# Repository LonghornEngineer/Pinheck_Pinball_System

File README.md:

Pinheck_Pinball_System
======================

Pinball system based off the PIC32 and Parallax Propeller microcontrollers

Created by:  
Benjamin J. Heckendorn  
Charlie Emery   
Parker Dillmann  

The Longhorn Engineer

http://longhornengineer.com/

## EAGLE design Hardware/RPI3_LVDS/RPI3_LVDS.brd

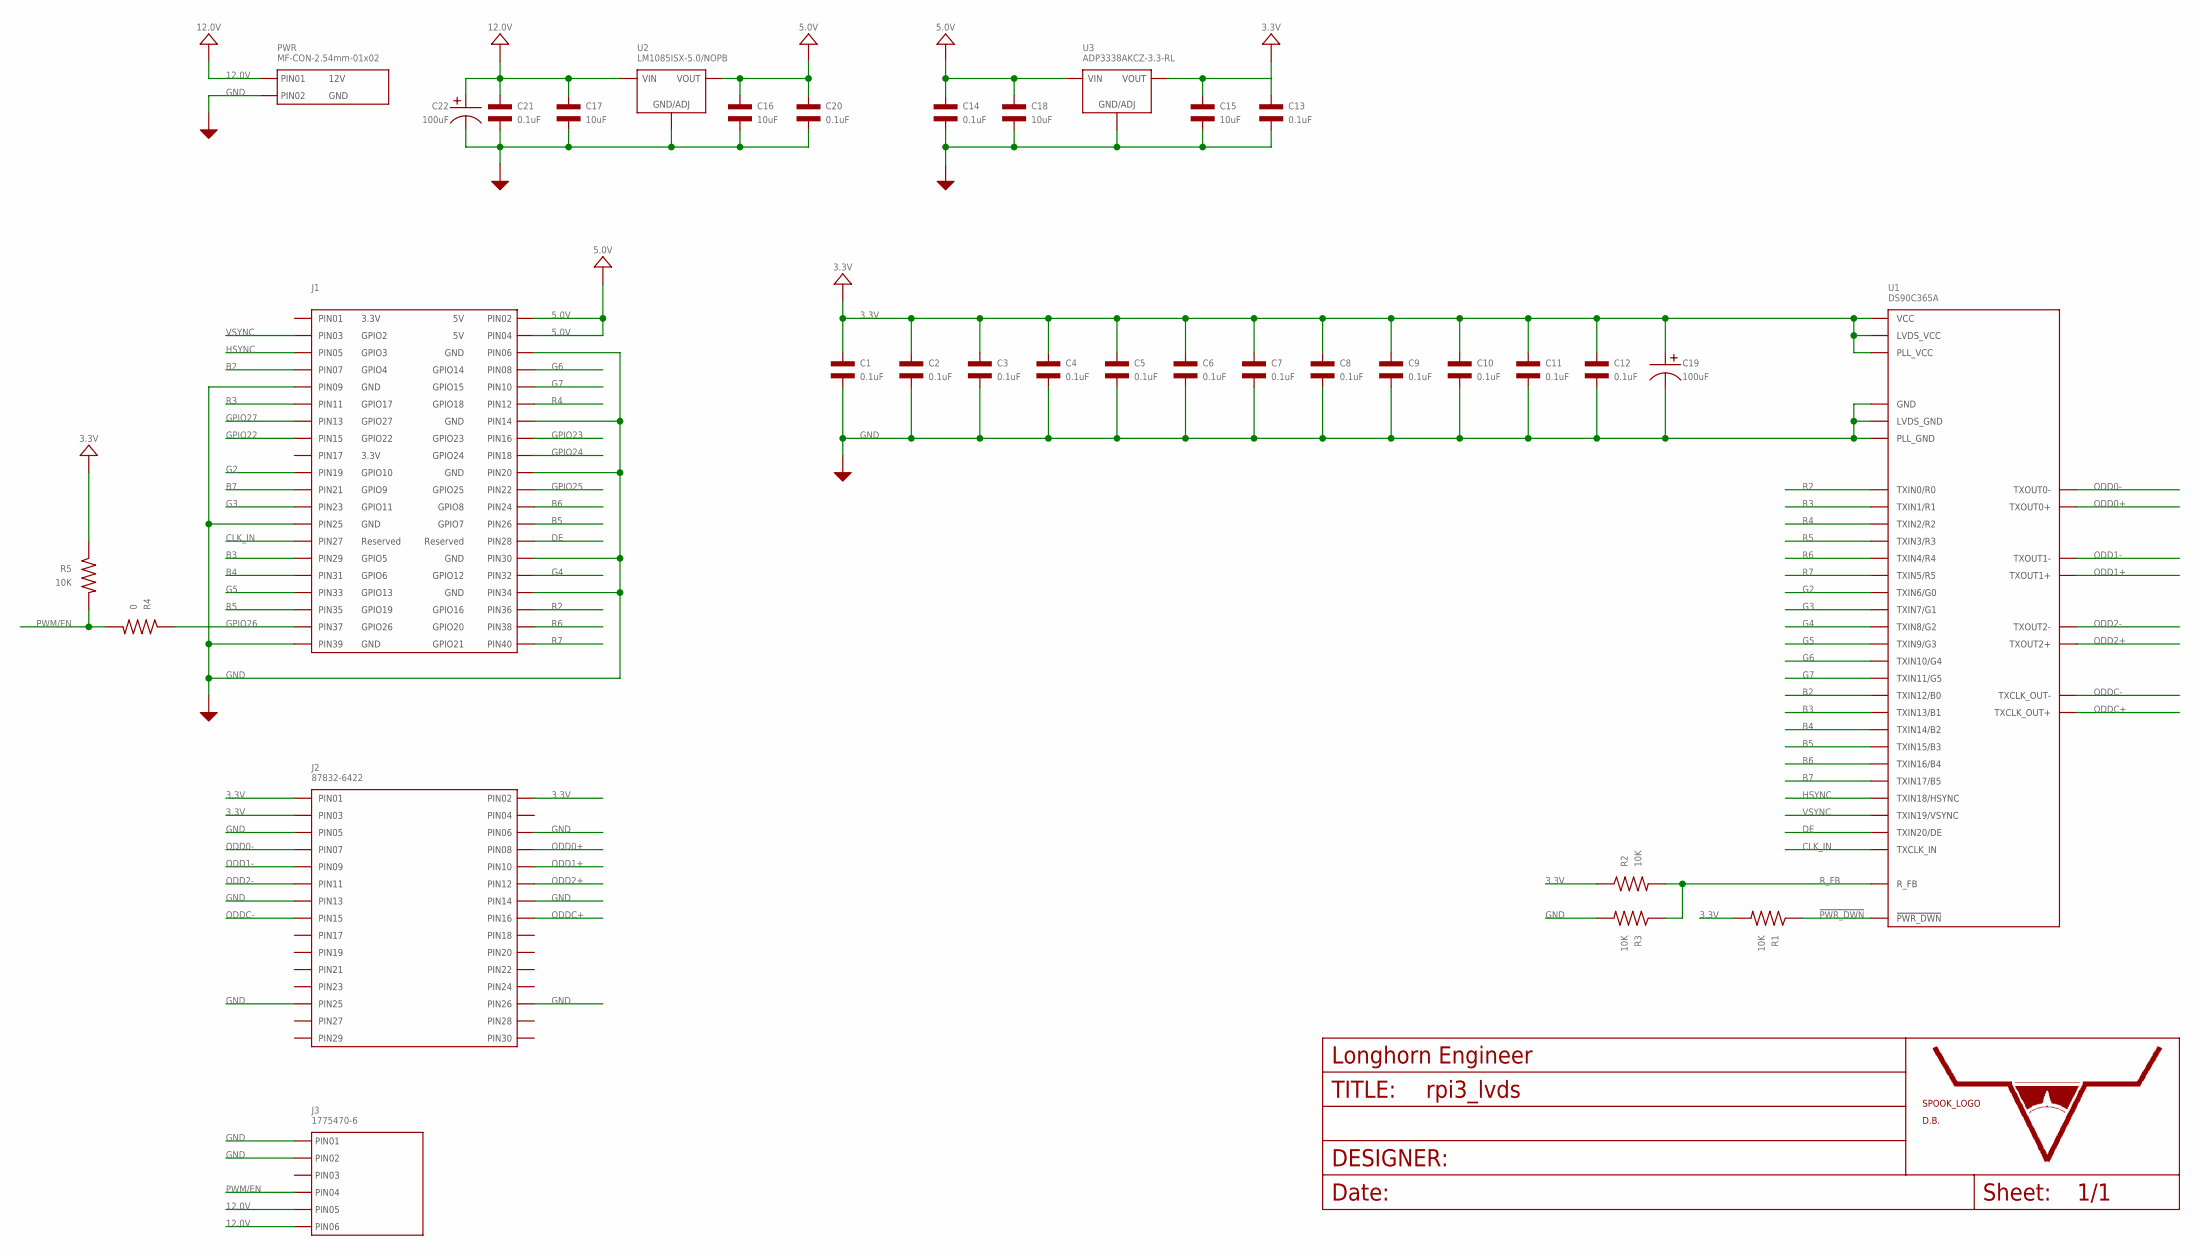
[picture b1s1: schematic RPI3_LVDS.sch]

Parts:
C1, C2, C3, C4, C5, C6, C7, C8, C9, C10, C11, C12, C13, C14, C20, C21: 0.1uF; C0603
C15, C16, C17, C18: 10uF; C1206
C19, C22: 100uF; CP6.3MM
J1: CON_02X202.54MM_PIN_HEADER; 2.54MM_02X20_PIN_HEADER
J2: 87832-6422
J3: 1775470-6
LOGO1: SPOOKY_LOGOSPOOKY_LOGO; SPOOKY_LOGO
PWR: MF-CON-2.54mm-01x02; PTH_2.54MM_01X02
R1, R2, R3, R5: 10K; R0603
R4: 0; R0603
U1: DS90C365A; DS90C365A_TSSOP-48
U2: LM1085ISX-5.0/NOPB; LM1085_TO-263-3
U3: ADP3338AKCZ-3.3-RL; ADP3338_SOT-223-3
U$14: LHE_FRAME
U$15: DB_LOGO_SILK_MEDIUM; DB_SILK_MEDIUM

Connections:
3.3V: C1.P$1, C2.P$1, C3.P$1, C4.P$1, C5.P$1, C6.P$1, C7.P$1, C8.P$1, C9.P$1, C10.P$1, C11.P$1, C12.P$1, C13.P$1, C15.P$1, C19.P$1, J2.P$1 (PIN0), J2.P$2 (PIN1), J2.P$3 (PIN2), R1.P$2, R2.P$1, R5.P$1, U1.P$2 (VCC), U1.P$8 (VCC), U1.P$21 (VCC), U1.P$29 (PLL_VCC), U1.P$37 (LVDS_VCC), U3.2 (OUT), U3.PAD (OUT)
5.0V: C14.P$1, C16.P$1, C18.P$1, C20.P$1, J1.2, J1.4, U2.P$2 (OUT), U2.P$4 (OUT), U3.3 (IN)
12.0V: C17.P$1, C21.P$1, C22.P$1, J3.P$5 (5), J3.P$6 (6), PWR.P$1 (PIN1), U2.P$3 (IN)
!PWR_DWN: R1.P$1, U1.P$27 (!PWR_DWN)
B2: J1.7, U1.P$13 (TXIN12/B0)
B3: J1.29, U1.P$15 (TXIN13/B1)
B4: J1.31, U1.P$16 (TXIN14/B2)
B5: J1.26, U1.P$18 (TXIN15/B3)
B6: J1.24, U1.P$19 (TXIN16/B4)
B7: J1.21, U1.P$20 (TXIN17/B5)
CLK_IN: J1.27, U1.P$26 (TXCLK_IN)
DE: J1.28, U1.P$25 (TXIN20/DE)
G2: J1.19, U1.P$4 (TXIN6/G0)
G3: J1.23, U1.P$6 (TXIN7/G1)
G4: J1.32, U1.P$7 (TXIN8/G2)
G5: J1.33, U1.P$9 (TXIN9/G3)
G6: J1.8, U1.P$10 (TXIN10/G4)
G7: J1.10, U1.P$12 (TXIN11/G5)
GND: C1.P$2, C2.P$2, C3.P$2, C4.P$2, C5.P$2, C6.P$2, C7.P$2, C8.P$2, C9.P$2, C10.P$2, C11.P$2, C12.P$2, C13.P$2, C14.P$2, C15.P$2, C16.P$2, C17.P$2, C18.P$2, C19.P$2, C20.P$2, C21.P$2, C22.P$2, J1.6, J1.9, J1.14, J1.20, J1.25, J1.30, J1.34, J1.39, J2.P$5 (PIN4), J2.P$6 (PIN5), J2.P$13 (PIN12), J2.P$14 (PIN13), J2.P$25 (PIN24), J2.P$26 (PIN25), J3.P$1 (1), J3.P$2 (2), PWR.P$2 (PIN2), R3.P$2, U1.P$5 (GND), U1.P$11 (GND), U1.P$17 (GND), U1.P$24 (GND), U1.P$28 (PLL_GND), U1.P$30 (PLL_GND), U1.P$31 (LVDS_GND), U1.P$36 (LVDS_GND), U1.P$42 (LVDS_GND), U1.P$46 (GND), U2.P$1 (GND), U3.1 (GND)
GPIO22: J1.15
GPIO23: J1.16
GPIO24: J1.18
GPIO25: J1.22
GPIO26: J1.37, R4.P$1
GPIO27: J1.13
HSYNC: J1.5, U1.P$22 (TXIN18/HSYNC)
ODD0+: J2.P$8 (PIN7), U1.P$40 (TXOUT0+)
ODD0-: J2.P$7 (PIN6), U1.P$41 (TXOUT0-)
ODD1+: J2.P$10 (PIN9), U1.P$38 (TXOUT1+)
ODD1-: J2.P$9 (PIN8), U1.P$39 (TXOUT1-)
ODD2+: J2.P$12 (PIN11), U1.P$34 (TXOUT2+)
ODD2-: J2.P$11 (PIN10), U1.P$35 (TXOUT2-)
ODDC+: J2.P$16 (PIN15), U1.P$32 (TXCLK_OUT+)
ODDC-: J2.P$15 (PIN14), U1.P$33 (TXCLK_OUT-)
PWM/EN: J3.P$4 (4), R4.P$2, R5.P$2
R2: J1.36, U1.P$44 (TXIN0/R0)
R3: J1.11, U1.P$45 (TXIN1/R1)
R4: J1.12, U1.P$47 (TXIN2/R2)
R5: J1.35, U1.P$48 (TXIN3/R3)
R6: J1.38, U1.P$1 (TXIN4/R4)
R7: J1.40, U1.P$3 (TXIN5/R5)
R_FB: R2.P$2, R3.P$1, U1.P$14 (R_FB)
VSYNC: J1.3, U1.P$23 (TXIN19/VSYNC)

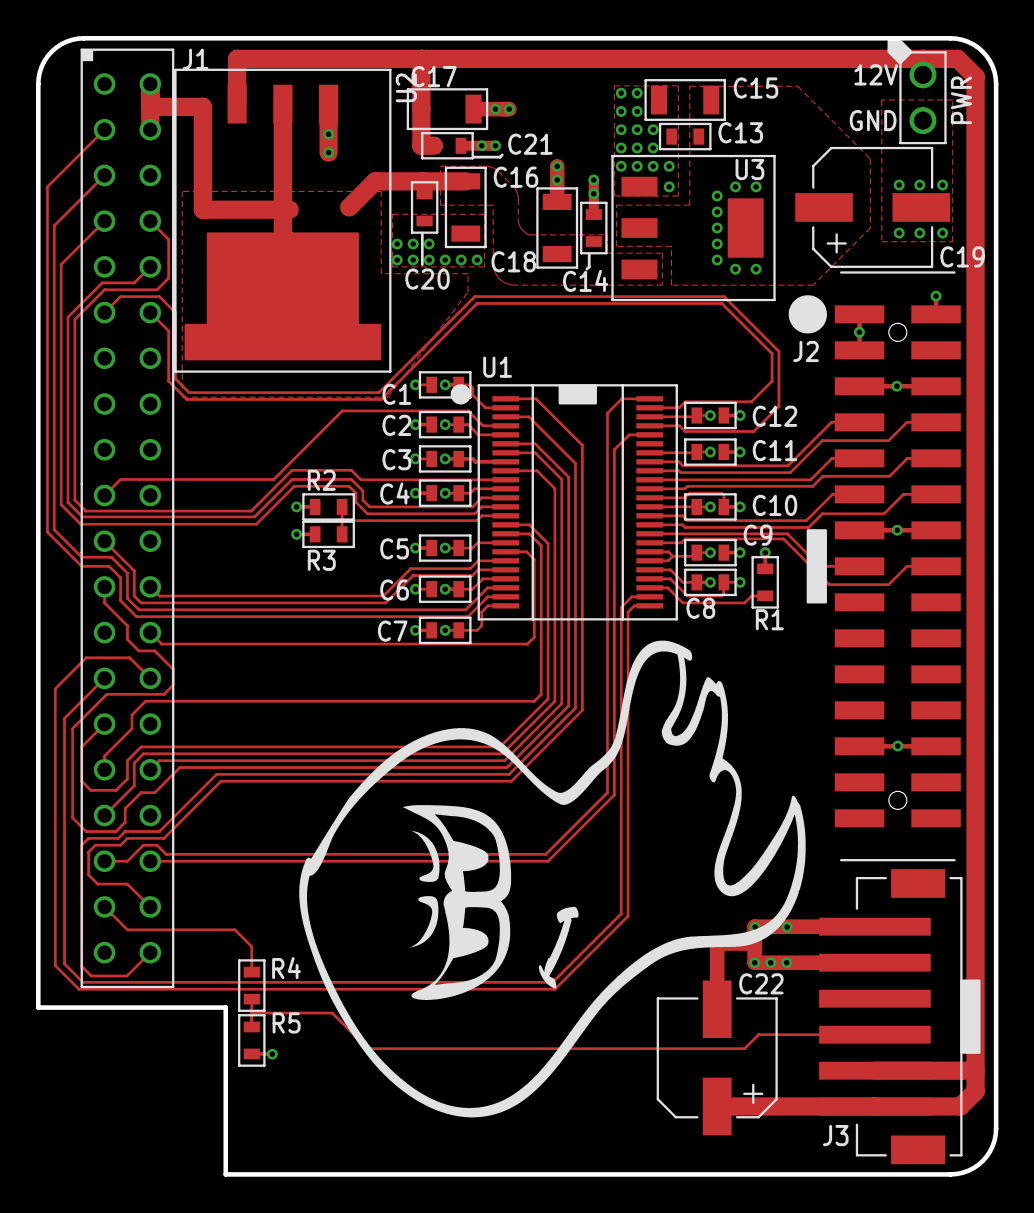
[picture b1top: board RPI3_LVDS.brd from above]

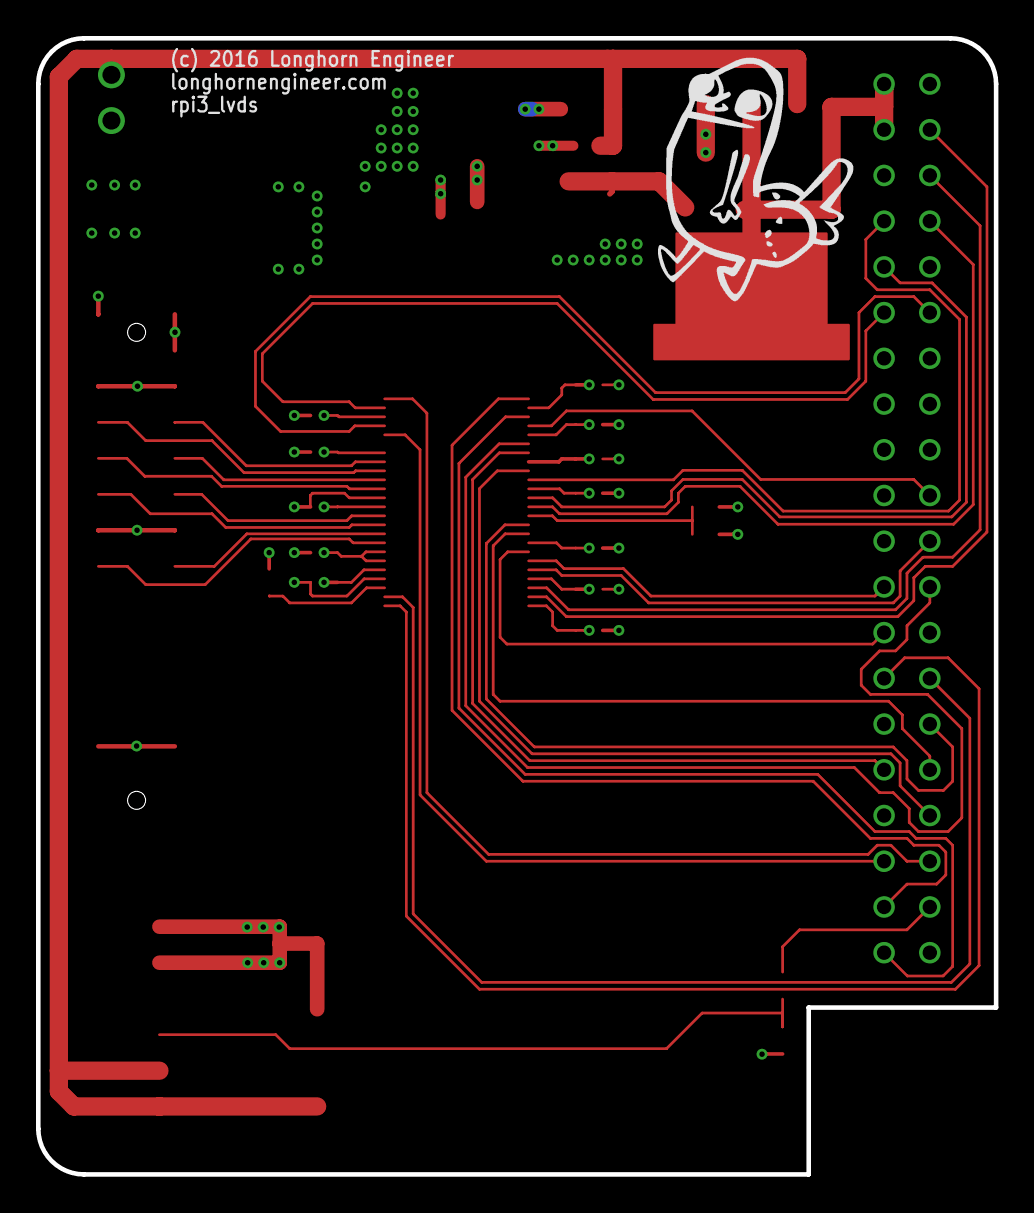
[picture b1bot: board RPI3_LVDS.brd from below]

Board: 4 copper layers, 53.2 x 63.1 mm, 37 parts (2 on the bottom side), 38 nets.

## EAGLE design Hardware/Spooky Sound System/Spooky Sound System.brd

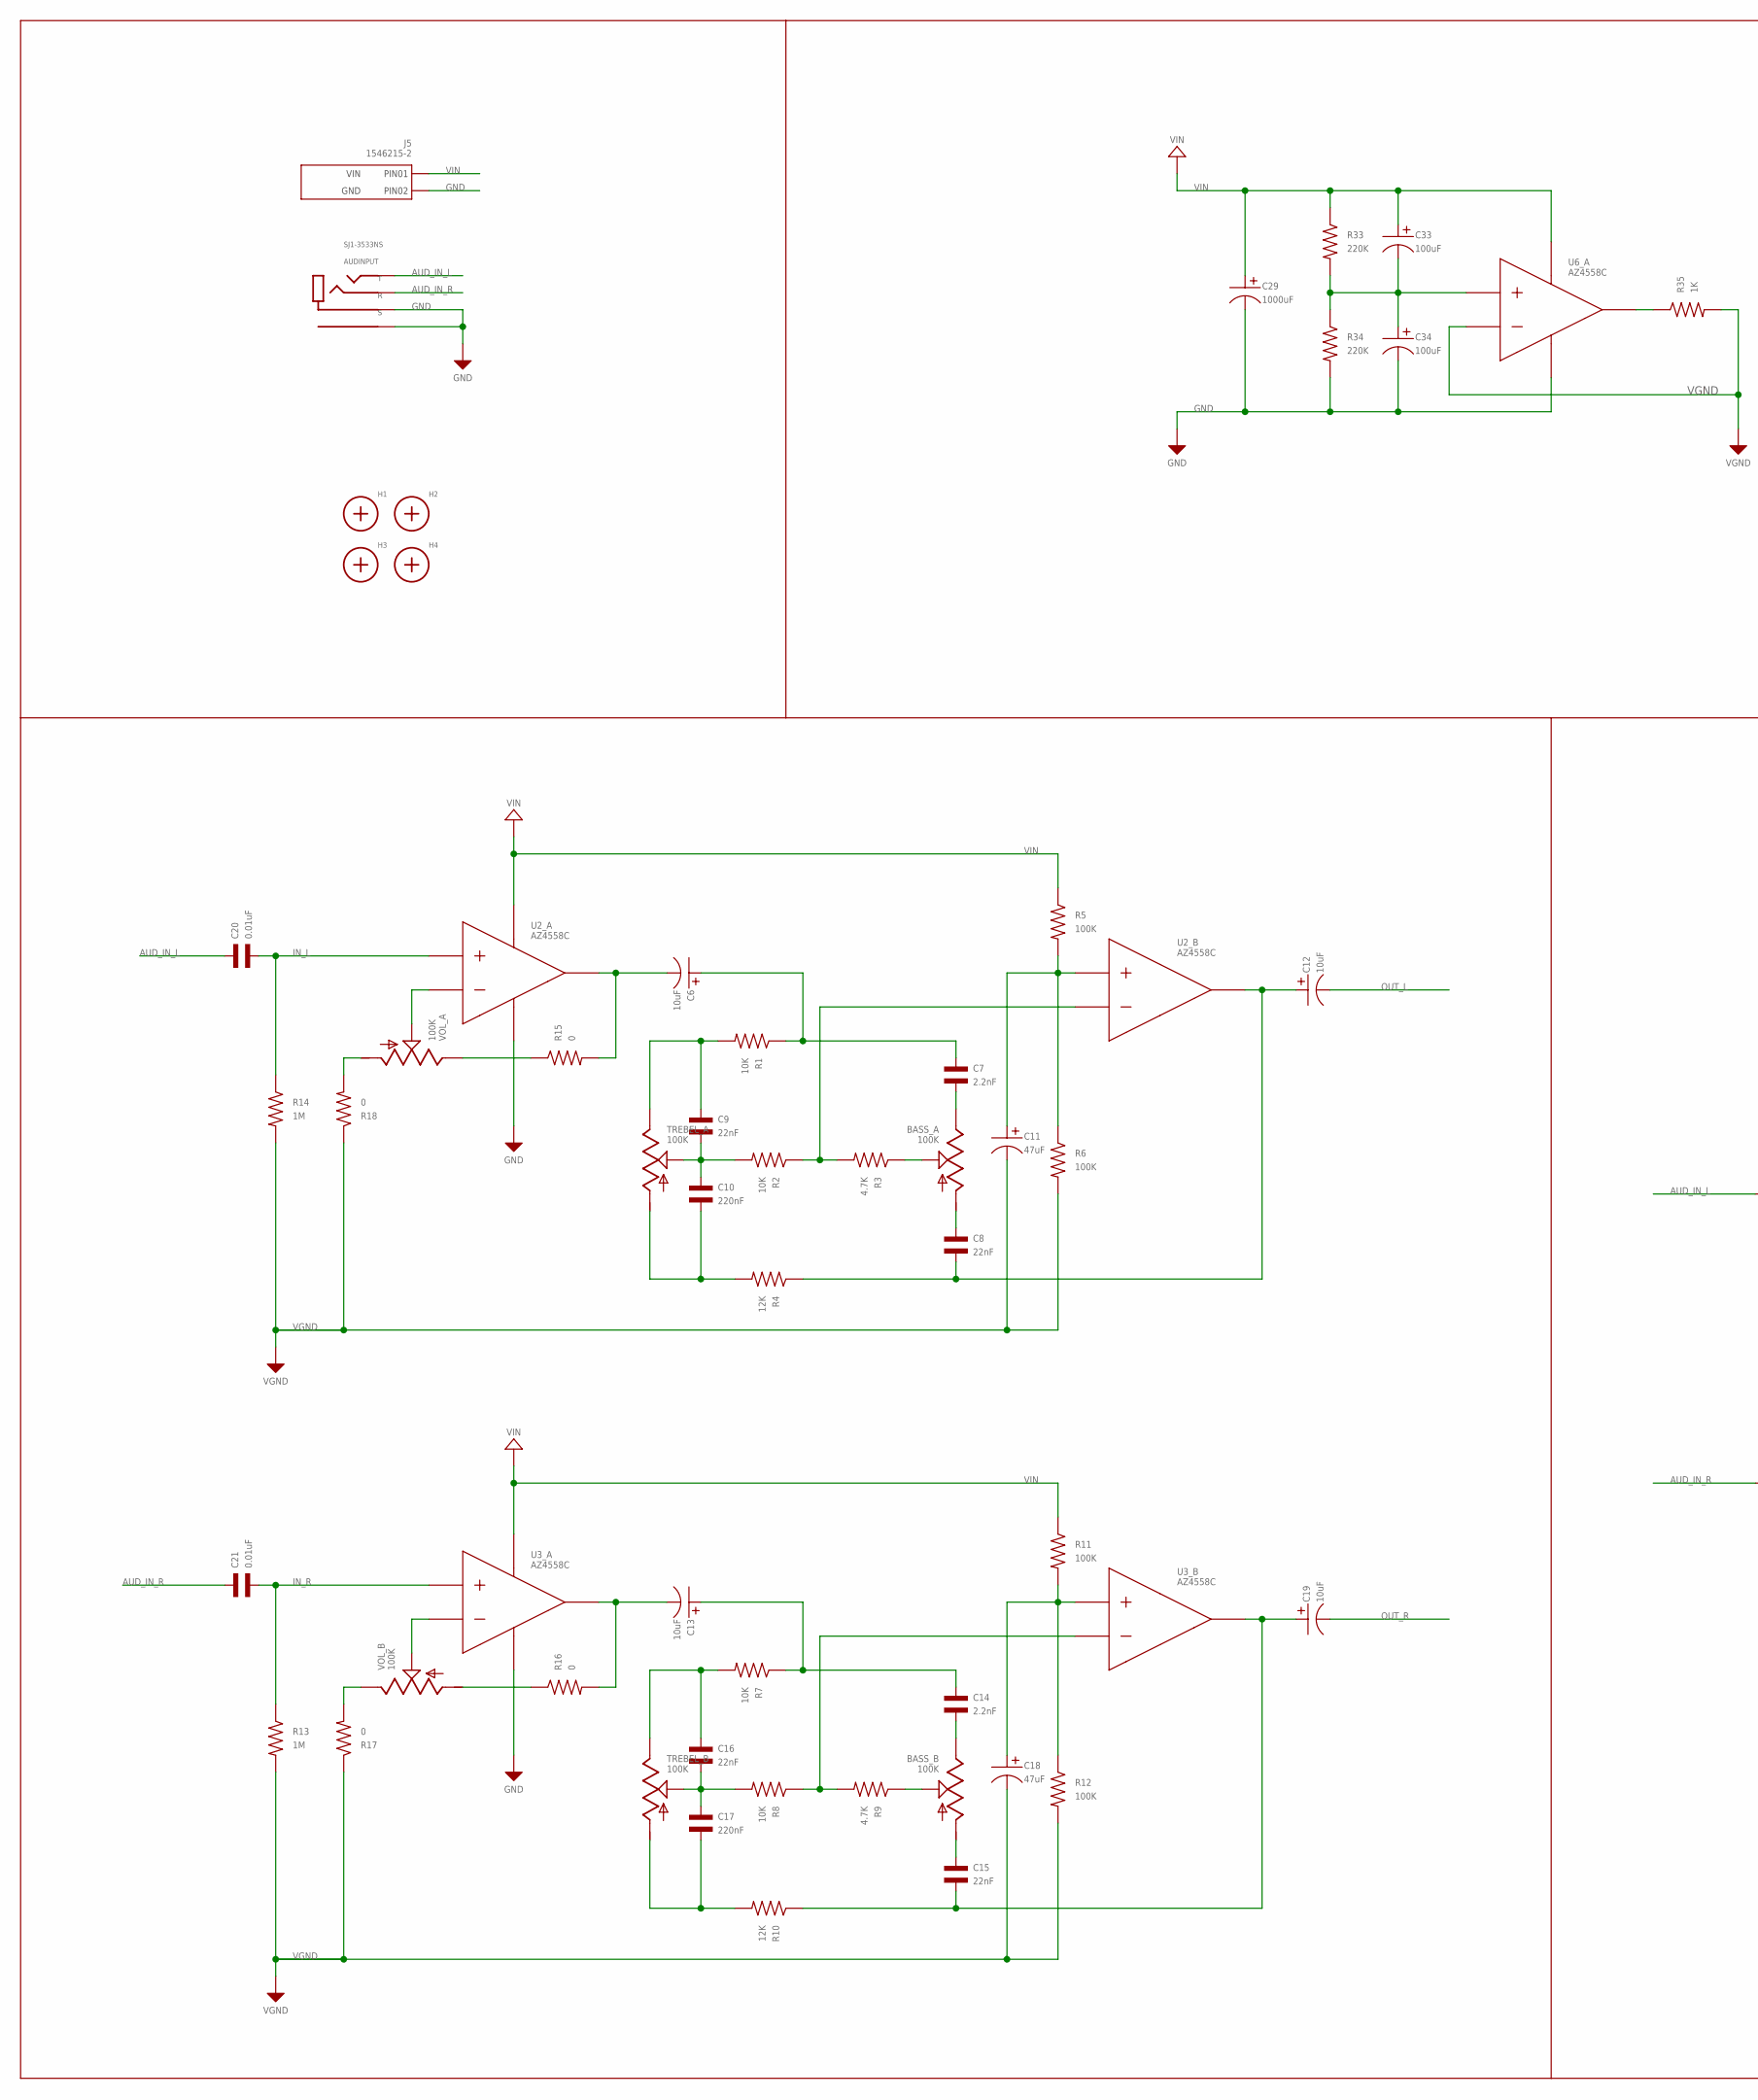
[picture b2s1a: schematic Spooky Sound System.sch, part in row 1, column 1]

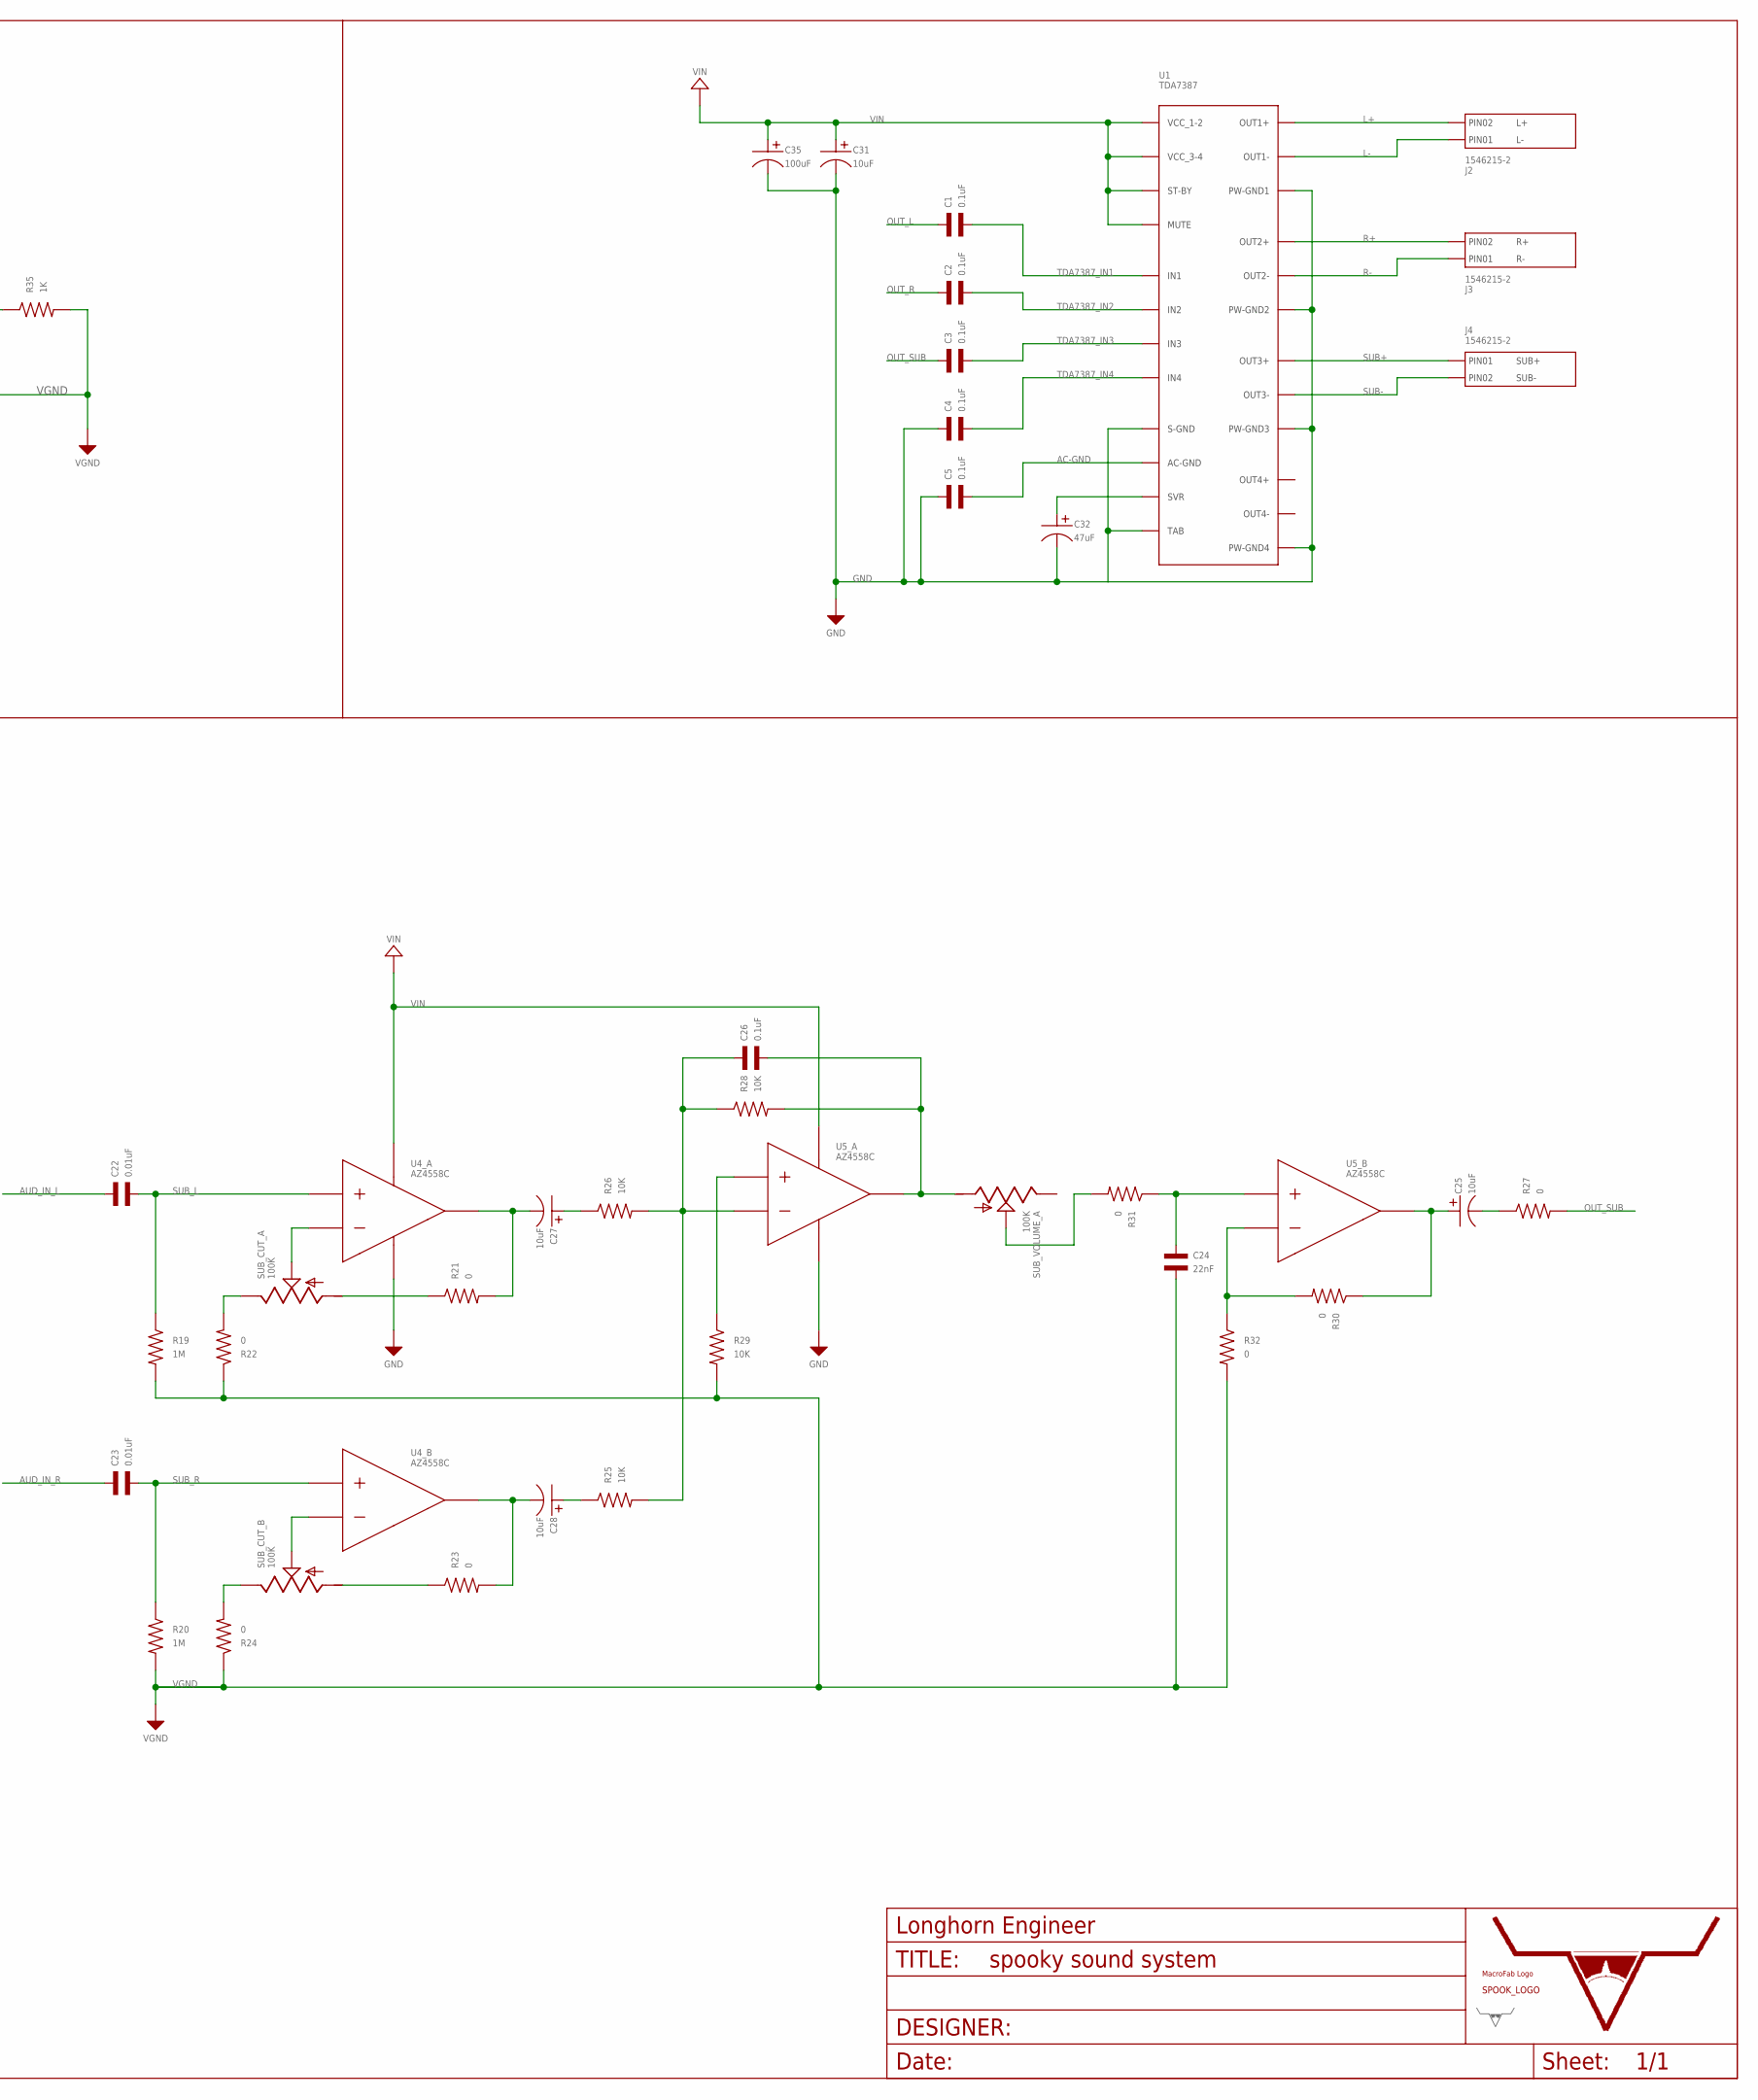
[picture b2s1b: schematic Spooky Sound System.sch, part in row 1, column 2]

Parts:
AUDINPUT: SJ1-3533NS
BASS: 100K; DUAL_TAPER_POTENTIOMETER
C1, C2, C3, C4, C5: 0.1uF; C1206; MPN VJ1206Y104JXBTW1BC
C6, C12, C13, C19, C25, C27, C28, C31: 10uF; CP4MM; MPN MF-CAP-4MM-10uF
C7, C14: 2.2nF; C0805
C8, C9, C15, C16, C24: 22nF; C0805
C10, C17: 220nF; C0805
C11, C18, C32: 47uF; CP6.3MM; MPN MF-CAP-6.3MM-47uF
C20, C21, C22, C23: 0.01uF; C1210; MPN CB017E0103KBA
C26: 0.1uF; C0805
C29: 1000uF; CP12.5MM; MPN MF-CAP-12.5MM-1000uF
C33, C34, C35: 100uF; CP6.3MM; MPN MF-CAP-6.3MM-100uF
H1, H2, H3, H4: MOUNT_HOLE150MIL; MOUNT_HOLE_150MIL
J2, J3, J4, J5: 1546215-2
LOGO1: SPOOKY_LOGOSPOOKY_LOGO; SPOOKY_LOGO
R1, R2, R7, R8, R25, R26, R28, R29: 10K; R0805
R3, R9: 4.7K; R0805
R4, R10: 12K; R0805
R5, R6, R11, R12: 100K; R0805
R13, R14, R19, R20: 1M; R0805
R15, R16, R17, R18, R21, R22, R23, R24, R27, R30, R31, R32: 0; R0805
R33, R34: 220K; R0805
R35: 1K; R0805
SUB_CUT: 100K; DUAL_TAPER_POTENTIOMETER
SUB_VOLUME: 100K; DUAL_TAPER_POTENTIOMETER
TREBEL: 100K; DUAL_TAPER_POTENTIOMETER
U1: TDA7387; TDA7387-FLEXIWATT-25
U2, U3, U4, U5, U6: AZ4558C; AZ4558C_SOIC-8
U$17: LHE_FRAME
U$18: LHE_LOGOLHE_LOGO; LHE_LOGO
U$19: MF_LOGOLOGO_TEXT; MF_LOGO_TEXT
VOL: 100K; DUAL_TAPER_POTENTIOMETER

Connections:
AC-GND: C5.P$2, U1.P$16 (AC-GND)
AUD_IN_L: AUDINPUT.2_A (T), AUDINPUT.2_B (T), C20.P$1, C22.P$1
AUD_IN_R: AUDINPUT.3_A (R), AUDINPUT.3_B (R), C21.P$1, C23.P$1
GND: AUDINPUT.1_A (S), AUDINPUT.1_B (S), AUDINPUT.S1 (SHIELD), AUDINPUT.S2 (SHIELD), AUDINPUT.S3 (SHIELD), AUDINPUT.S4 (SHIELD), AUDINPUT.S5 (SHIELD), AUDINPUT.S6 (SHIELD), C4.P$1, C5.P$1, C29.P$2, C31.P$2, C32.P$2, C34.P$2, C35.P$2, J5.P$2 (PIN2), R34.P$2, U1.P$1 (TAB), U1.P$2 (PW-GND2), U1.P$8 (PW-GND1), U1.P$13 (S-GND), U1.P$18 (PW-GND3), U1.P$24 (PW-GND4), U2.4 (VEE), U3.4 (VEE), U4.4 (VEE), U5.4 (VEE), U6.4 (VEE)
IN_L: C20.P$2, R14.P$1, U2.3 (INPUT_1+)
IN_R: C21.P$2, R13.P$1, U3.3 (INPUT_1+)
L+: J2.P$2 (PIN2), U1.P$9 (OUT1+)
L-: J2.P$1 (PIN1), U1.P$7 (OUT1-)
unnamed: C6.P$2, R15.P$2, U2.1 (OUTPUT_1)
unnamed: C6.P$1, C7.P$1, R1.P$1
unnamed: C9.P$1, R1.P$2, TREBEL.1A (1)
unnamed: C9.P$2, C10.P$1, R2.P$2, TREBEL.2A (2)
unnamed: C10.P$2, R4.P$2, TREBEL.3A (3)
unnamed: R2.P$1, R3.P$2, U2.6 (INPUT_2-)
unnamed: BASS.2A (2), R3.P$1
unnamed: BASS.1A (1), C7.P$2
unnamed: BASS.3A (3), C8.P$1
unnamed: C8.P$2, C12.P$1, R4.P$1, U2.7 (OUTPUT_2)
unnamed: C11.P$1, R5.P$2, R6.P$1, U2.5 (INPUT_2+)
unnamed: C13.P$2, R16.P$2, U3.1 (OUTPUT_1)
unnamed: C13.P$1, C14.P$1, R7.P$1
unnamed: C16.P$1, R7.P$2, TREBEL.1B (1)
unnamed: C16.P$2, C17.P$1, R8.P$2, TREBEL.2B (2)
unnamed: C17.P$2, R10.P$2, TREBEL.3B (3)
unnamed: R8.P$1, R9.P$2, U3.6 (INPUT_2-)
unnamed: BASS.2B (2), R9.P$1
unnamed: BASS.1B (1), C14.P$2
unnamed: BASS.3B (3), C15.P$1
unnamed: C15.P$2, C19.P$1, R10.P$1, U3.7 (OUTPUT_2)
unnamed: C18.P$1, R11.P$2, R12.P$1, U3.5 (INPUT_2+)
unnamed: C27.P$2, R21.P$2, U4.1 (OUTPUT_1)
unnamed: R21.P$1, SUB_CUT.3A (3)
unnamed: R16.P$1, VOL.3B (3)
unnamed: R17.P$2, VOL.1B (1)
unnamed: C28.P$2, R23.P$2, U4.7 (OUTPUT_2)
unnamed: R23.P$1, SUB_CUT.3B (3)
unnamed: C26.P$1, R25.P$2, R26.P$2, R28.P$1, U5.2 (INPUT_1-)
unnamed: C26.P$2, R28.P$2, SUB_VOLUME.3A (3), U5.1 (OUTPUT_1)
unnamed: R29.P$1, U5.3 (INPUT_1+)
unnamed: R31.P$2, SUB_VOLUME.2A (2)
unnamed: R30.P$2, R32.P$1, U5.6 (INPUT_2-)
unnamed: C25.P$1, R30.P$1, U5.7 (OUTPUT_2)
unnamed: SUB_CUT.2A (2), U4.2 (INPUT_1-)
unnamed: R22.P$2, SUB_CUT.1A (1)
unnamed: R24.P$2, SUB_CUT.1B (1)
unnamed: SUB_CUT.2B (2), U4.6 (INPUT_2-)
unnamed: U3.2 (INPUT_1-), VOL.2B (2)
unnamed: R18.P$2, VOL.3A (3)
unnamed: U2.2 (INPUT_1-), VOL.2A (2)
unnamed: R15.P$1, VOL.1A (1)
unnamed: C24.P$1, R31.P$1, U5.5 (INPUT_2+)
unnamed: C25.P$2, R27.P$1
unnamed: C27.P$1, R26.P$1
unnamed: C28.P$1, R25.P$1
unnamed: C33.P$2, C34.P$1, R33.P$2, R34.P$1, U6.3 (INPUT_1+)
unnamed: R35.P$1, U6.1 (OUTPUT_1)
unnamed: C32.P$1, U1.P$10 (SVR)
OUT_L: C1.P$1, C12.P$2
OUT_R: C2.P$1, C19.P$2
OUT_SUB: C3.P$1, R27.P$2
R+: J3.P$2 (PIN2), U1.P$5 (OUT2+)
R-: J3.P$1 (PIN1), U1.P$3 (OUT2-)
SUB+: J4.P$1 (PIN1), U1.P$17 (OUT3+)
SUB-: J4.P$2 (PIN2), U1.P$19 (OUT3-)
SUB_L: C22.P$2, R19.P$1, U4.3 (INPUT_1+)
SUB_R: C23.P$2, R20.P$1, U4.5 (INPUT_2+)
TDA7387_IN1: C1.P$2, U1.P$11 (IN1)
TDA7387_IN2: C2.P$2, U1.P$12 (IN2)
TDA7387_IN3: C3.P$2, U1.P$15 (IN3)
TDA7387_IN4: C4.P$2, U1.P$14 (IN4)
VGND: C11.P$2, C18.P$2, C24.P$2, R6.P$2, R12.P$2, R13.P$2, R14.P$2, R17.P$1, R18.P$1, R19.P$2, R20.P$2, R22.P$1, R24.P$1, R29.P$2, R32.P$2, R35.P$2, U6.2 (INPUT_1-)
VIN: C29.P$1, C31.P$1, C33.P$1, C35.P$1, J5.P$1 (PIN1), R5.P$1, R11.P$1, R33.P$1, U1.P$4 (ST-BY), U1.P$6 (VCC_1-2), U1.P$20 (VCC_3-4), U1.P$22 (MUTE), U2.8 (VCC), U3.8 (VCC), U4.8 (VCC), U5.8 (VCC), U6.8 (VCC)

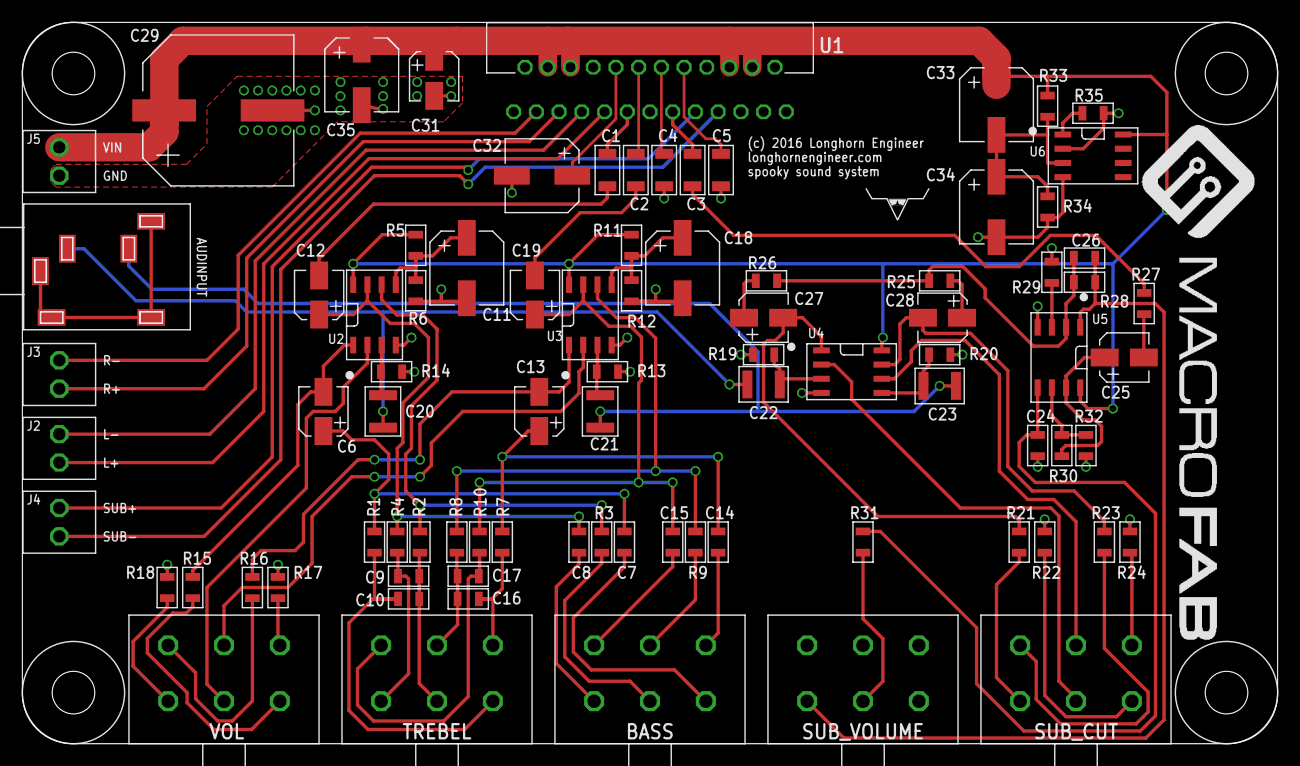
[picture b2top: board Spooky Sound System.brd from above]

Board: 4 copper layers, 112.3 x 64.5 mm, 93 parts (1 on the bottom side), 72 nets.

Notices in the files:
parts and their libraries:
SparkFun-DigitalIC: Licensing: CC v3.0 Share-Alike You are welcome to use this library for commercial purposes.
PP_Aesthetics: (c) 2016 Longhorn Engineer
